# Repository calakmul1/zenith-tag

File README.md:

# Zenith Tag - NFC Flight Altitude Logger

Zenith Tag is a compact embedded altitude logger built around the NXP NHS3100 and Bosch BMP388.
It captures relative max flight altitude from barometric pressure and writes the result as an NFC URI record, so the value can be read by a phone with no wired interface.

<table align="center">
	<tr>
		<td align="center" valign="middle" width="74%">
			
		</td>
		<td align="center" valign="middle" width="26%">
			
		</td>
	</tr>
	<tr>
		<td align="center"><sub>PCB Layout</sub></td>
		<td align="center"><sub>Altitude Meter UI</sub></td>
	</tr>
</table>

## What This Repository Contains

This repository is split into three main parts:

- `hw/`: KiCad design files, custom libraries, 3D models, and datasheets
- `sw/`: NHS3100 firmware project (MCUXpresso style) and source modules
- `web/`: Vue 3 web app served from the NFC URI that visualises the recorded altitude

## High-Level Features

- BMP388 pressure and temperature acquisition over I2C
- Full BMP388 calibration and compensation implementation in firmware
- Relative altitude computation using barometric equation
- Push-button controlled measurement session
- LED status signaling (idle, actively measuring, and error indication)
- NFC Type-2 compatible NDEF URI payload written to NHS3100 shared memory
- Web app landing page that parses the height query parameter and renders an animated altitude bar

## Repository Structure

### Hardware (`hw/`)

- Main KiCad project files:
	- `hw/hw.kicad_sch`
	- `hw/hw.kicad_pcb`
	- `hw/hw.kicad_pro`
- Custom part libraries:
	- `hw/footprints/` and `hw/hw.pretty/` for footprint definitions
	- `hw/symbols/` for custom symbol definitions
	- `hw/models/` for STEP 3D models
- Engineering references:
	- `hw/datasheets/` for component PDFs and reference image files
	- `hw/calculations/NFC-Antenna-Calculation.xlsx` for antenna-related design calculations

### Firmware (`sw/`)

- Application source tree: `sw/src/`
- Core application entry point: `sw/src/main.c`
- Board and low-level init:
	- `sw/src/board/inc/board.h`
	- `sw/src/board/src/board.c`
- Functional components:
	- `sw/src/components/button/`
	- `sw/src/components/led/`
	- `sw/src/components/pressure/`
	- `sw/src/components/nfc/`
- Device/library code:
	- `sw/src/lib/lib_chip_nss/`
	- `sw/src/lib/startup/`

### Web App (`web/`)

A Vite + Vue 3 single-page app hosted at the NFC URI target.

- Entry point: `web/src/App.vue`
- Reads the `height` query parameter from the URL (e.g. `?height=12.34`)
- Renders an animated vertical bar showing the recorded altitude, clamped to ±30 m
- Styled with Bulma

To run locally:

```sh
cd web
npm install
npm run dev
```

To build for production:

```sh
npm run build
```

## Firmware Behavior

The main loop in `sw/src/main.c` follows this sequence:

1. Initialize board/peripherals and BMP388.
2. Wait for button press to start a measurement session.
3. Collect a short pre-takeoff pressure baseline (`PRE_TAKEOFF_MEASUREMENTS`).
4. Repeatedly sample pressure while session is active, tracking the minimum pressure reached.
5. End session with a second button press.
6. Compute signed relative altitude from both `pressure_min` and `pressure_max` versus baseline pressure, choose the larger magnitude, then apply a `-0.50 m` offset.
7. Store the measured value over NFC as a URI query parameter: `https://example.com/?height=<value>`.

Current default timing constants are defined in `sw/src/config.h`:

- Debounce: 5 ms
- Measurement interval: 20 ms
- LED toggle during active measurement: 500 ms
- Baseline sample count: 10

## Hardware/Firmware Interface Summary

- MCU: NXP NHS3100 (integrated NFC + Cortex-M0+)
- Pressure sensor: Bosch BMP388 on I2C address `0x77`
- Key pin usage in firmware:
	- `PIO0_1`: button input
	- `PIO0_2`: status LED output
	- `PIO0_4`: I2C SCL
	- `PIO0_5`: I2C SDA

## NFC Output Format

The NFC module (`sw/src/components/nfc/nfc.c`) writes a compact NDEF URI record into NHS3100 NFC shared memory.
The payload encodes a URL in this form: `https://example.com/?height=<value>`.

Example payload:

`https://example.com/?height=12.34`

## Build and Flash Notes

This project is structured like an MCUXpresso/Eclipse embedded project.

- Recommended workflow:
	- Import the `sw/` project into MCUXpresso IDE
	- Build using IDE-managed toolchain/configuration
	- Program/debug using LinkServer and the provided launch configuration
- Command-line makefiles are auto-generated and may contain absolute machine-specific paths in linker/library references.

## Included References

- Component datasheets and design references: `hw/datasheets/`

## Typical Use

1. Manufacture the PCB.
2. Configure GUI_BASE_URL in `config.h` with the URL of the web application that should open after the NFC tag is scanned.
3. Build and flash the firmware to the NHS3100 board.
4. Power on the tag and wait for idle-ready indication.
5. Press the button to start logging.
6. Press the button again to stop logging.
7. Tap a phone to the NFC antenna area — the phone opens the stored URI in a browser.
8. The web app reads the `height` query parameter and displays the recorded altitude.

---

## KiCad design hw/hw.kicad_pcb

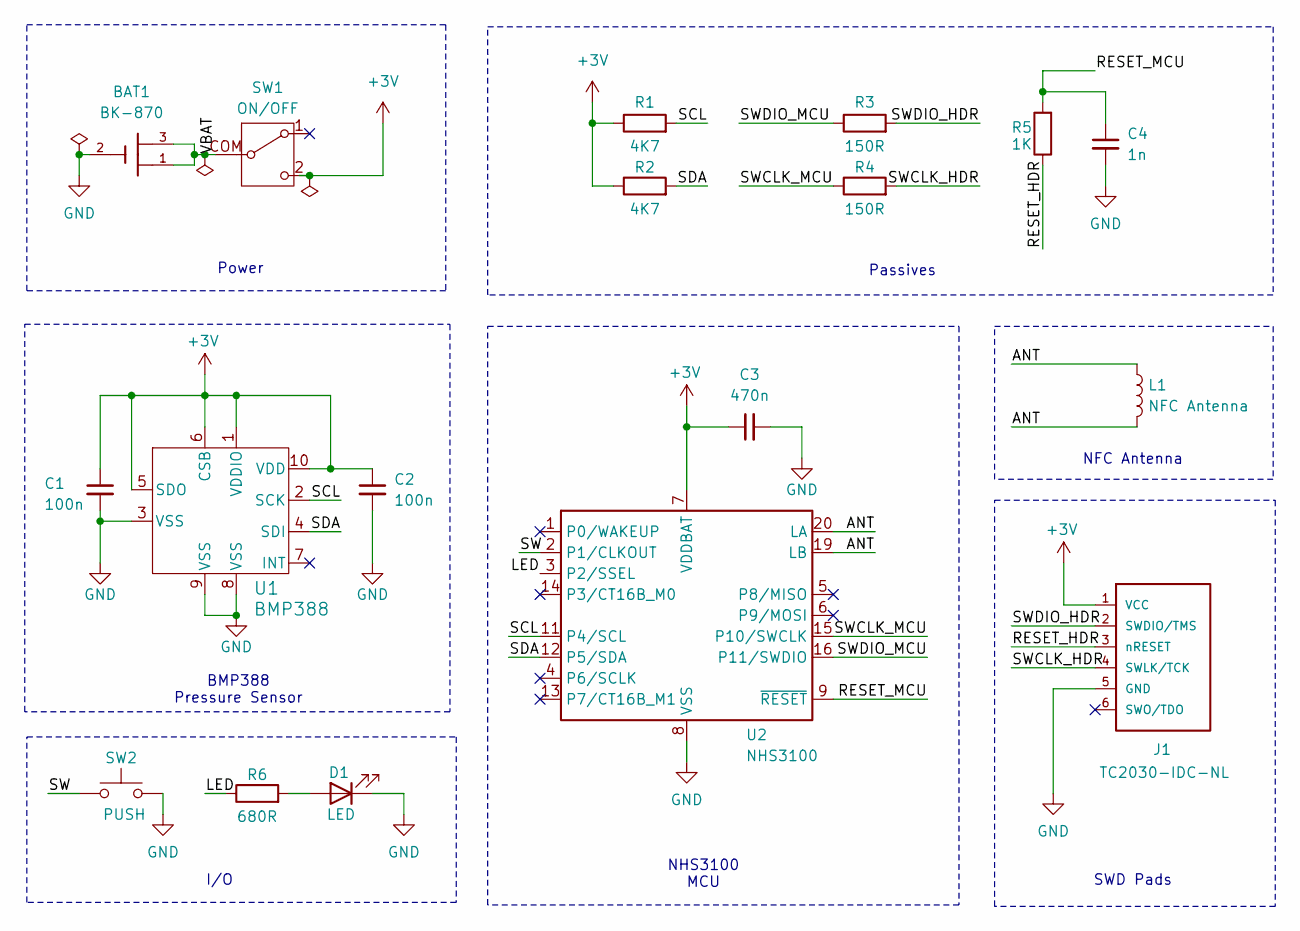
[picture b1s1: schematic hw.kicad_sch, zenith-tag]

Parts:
BAT1: BK-870; BK870; LCSC C6470567
C1: 100n; C_0402_1005Metric; LCSC C1525
C2: 100n; C_0402_1005Metric
C3: 470n; C_0402_1005Metric; LCSC C47339
C4: 1n; C_0402_1005Metric; LCSC C1523
D1: LED; LED_NCD0805R1_FNO; LCSC C84256
J1: TC2030-IDC-NL; TAG_TC2030-IDC-NL
L1: NFC Antenna; NFC_ANTENNA10x15
R1, R2: 4K7; R_0402_1005Metric; LCSC C25900
R3, R4: 150R; R_0402_1005Metric; LCSC C25082
R5: 1K; R_0402_1005Metric; LCSC C11702
R6: 680R; R_0402_1005Metric; LCSC C25130
SW1: ON/OFF; SK12D07VG4; LCSC C393937
SW2: PUSH; B3U-1000P_OMR; LCSC C231329
U1: BMP388; BMP388-QFN_BMP388_BOS; LCSC C779278
U2: NHS3100; NHS3100-QFN50P400X400X100-25N; LCSC C2654844

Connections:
+3V: C1.1, C2.1, C3.1, J1.1 (VCC), R1.1, R2.1, SW1.2 (C), U1.1 (VDDIO), U1.5 (SDO), U1.6 (CSB), U1.10 (VDD), U2.7 (VDDBAT)
/ANT: L1.1, L1.2, U2.19 (LB), U2.20 (LA)
/LED: R6.1, U2.3 (P2/SSEL)
/RESET_HDR: J1.3 (nRESET), R5.1
/RESET_MCU: C4.1, R5.2, U2.9 (~RESET)
/SCL: R1.2, U1.2 (SCK), U2.11 (P4/SCL)
/SDA: R2.2, U1.4 (SDI), U2.12 (P5/SDA)
/SW: SW2.1, U2.2 (P1/CLKOUT)
/SWCLK_HDR: J1.4 (SWLK/TCK), R4.2
/SWCLK_MCU: R4.1, U2.15 (P10/SWCLK)
/SWDIO_HDR: J1.2 (SWDIO/TMS), R3.2
/SWDIO_MCU: R3.1, U2.16 (P11/SWDIO)
/VBAT: BAT1.1, BAT1.3, SW1.COM (B)
GND: BAT1.2, C1.2, C2.2, C3.2, C4.2, D1.1 (K), J1.5 (GND), SW2.2, U1.3 (VSS), U1.8 (VSS), U1.9 (VSS), U2.8 (VSS), U2.17 (VSS), U2.18 (VSS), U2.21 (VSS), U2.22 (VSS), U2.23 (VSS), U2.24 (VSS), U2.25 (VSS)
unnamed: D1.2 (A), R6.2

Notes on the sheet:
SWD Pads
I/O
Power
NHS3100 MCU
NFC Antenna
Passives
BMP388 Pressure Sensor

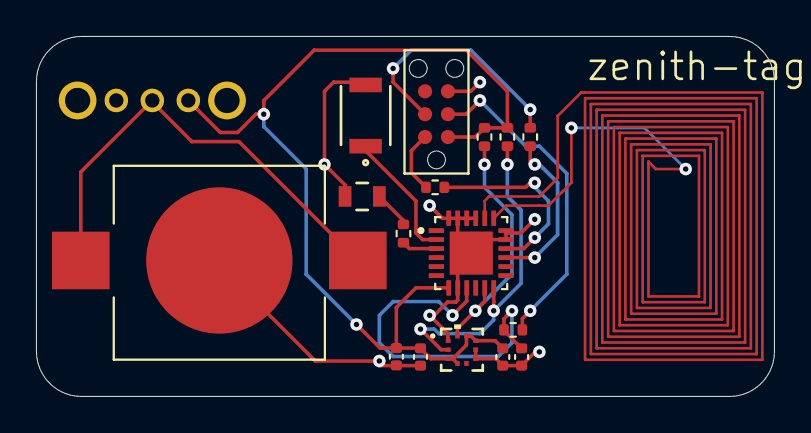
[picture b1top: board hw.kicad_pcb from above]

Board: 2 copper layers, 41.0 x 20.0 mm, 18 parts (0 on the bottom side), 15 nets.
